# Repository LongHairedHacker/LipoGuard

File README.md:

LipoGuard
=========
A simple deep discharge protection for all types of rechargeable batteries.

Licence
-------
The schematics and pcb layout files in hardware are released
under the *CERN Open Hardware Licence v1.2*, except for my personal logo.
Please remove my logo, if I am not involved in your project.

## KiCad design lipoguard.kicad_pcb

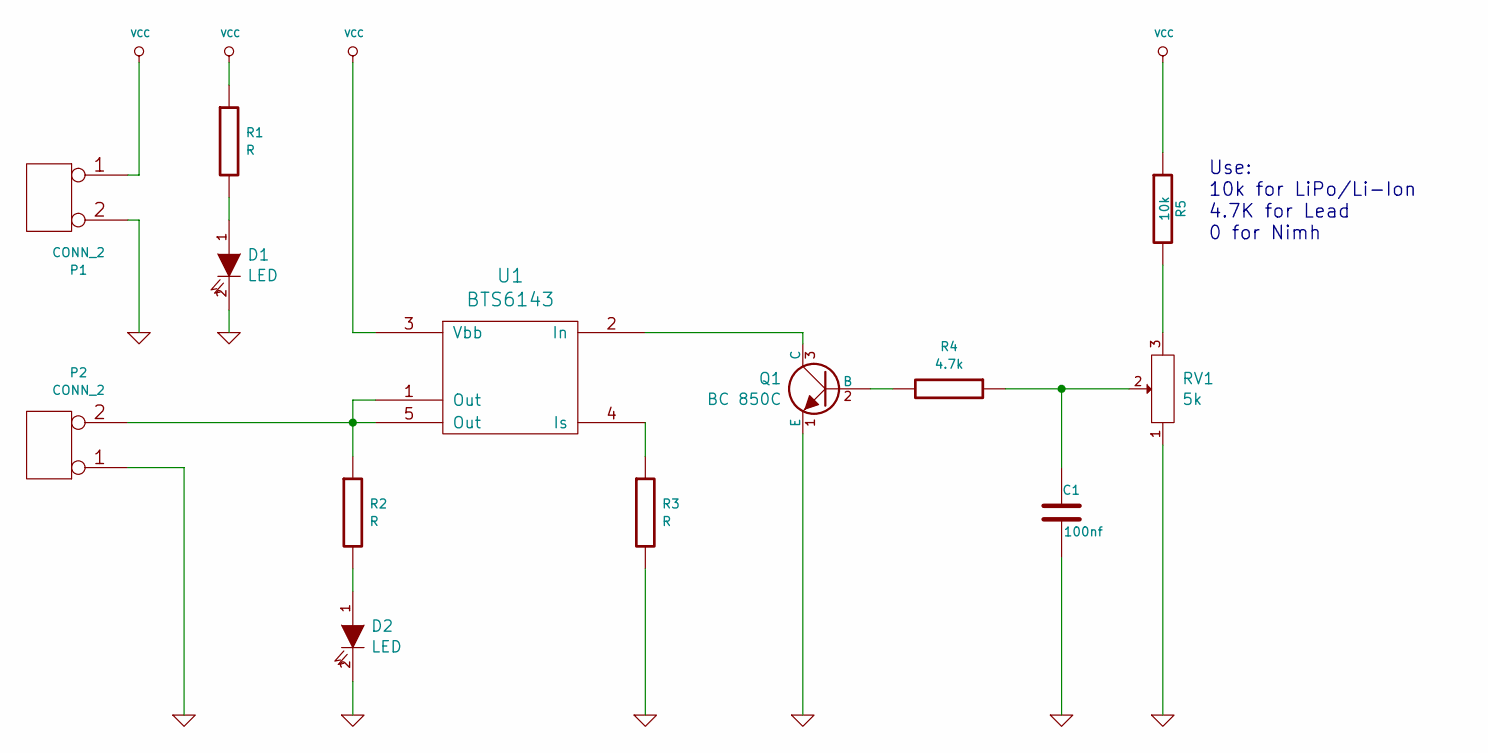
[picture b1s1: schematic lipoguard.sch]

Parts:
C1: 100nf; SM0603
D1, D2: LED; SM0603
P1, P2: CONN_2; bornier2
Q1: BC 850C; sot23BEC
R1, R2, R3: R; SM0603
R4: 4.7k; SM0603
R5: 10k; SM0603
RV1: 5k; trimmer1
U1: BTS6143; TO252-5L

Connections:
GND: C1.2, D1.2 (K), D2.2 (K), P1.2 (PM), P2.1, Q1.1 (E), R3.2, RV1.1
unnamed: C1.1, R4.1, RV1.2
unnamed: D1.1 (A), R1.2
unnamed: D2.1 (A), R2.2
unnamed: P2.2 (PM), R2.1, U1.1 (Out), U1.5 (Out)
unnamed: Q1.2 (B), R4.2
unnamed: Q1.3 (C), U1.2 (In)
unnamed: R3.1, U1.4 (Is)
unnamed: R5.2, RV1.3
VCC: P1.1, R1.1, R5.1, U1.3 (Vbb)

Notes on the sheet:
Use: 10k for LiPo/Li-Ion 4.7K for Lead 0 for Nimh

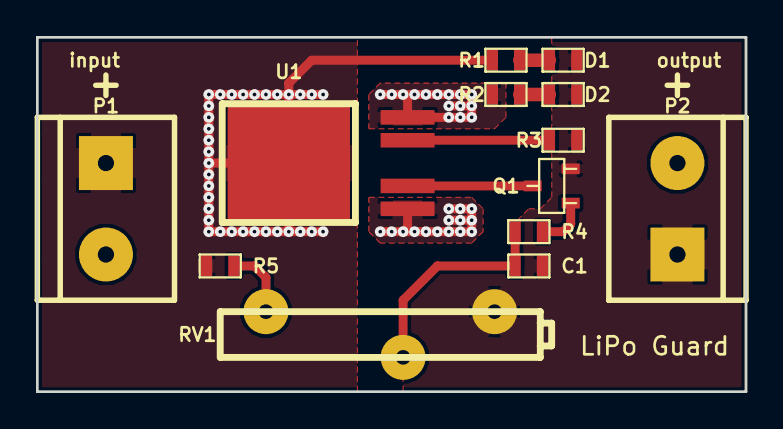
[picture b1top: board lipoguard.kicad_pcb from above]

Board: 2 copper layers, 39.4 x 19.7 mm, 13 parts (0 on the bottom side), 10 nets.

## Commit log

2016-10-03 Simplified schematic
2016-10-04 Finished cleaning up
2016-10-05 Cleaned up pcb
2016-10-05 Added resistor for better threshold adjustment
2016-10-05 Used smaller Logo
2016-10-05 Added gerbers
2016-10-06 Enhanced silkscreen
2016-10-06 Generated gerbers and panelized
2016-11-07 Updated symbols to new kicad libraries Added missing values Updated pdfs
2016-11-07 Added license

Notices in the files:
lipoguard.kicad_pcb:
CC-BY-SA 3.0
